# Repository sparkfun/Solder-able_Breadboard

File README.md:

Solder-able Breadboard
=======================

[ 
*Solder-able Breadboard(PRT-12070)*](https://www.sparkfun.com/products/12070)

This is a bare pcb that is the same size as a regular breadboard, along with the same connections and power rails.

Repository Contents
-------------------
* **/Hardware** - All Eagle design files (.brd, .sch)

License Information
-------------------
The hardware is released under [Creative Commons Share-alike 3.0](http://creativecommons.org/licenses/by-sa/3.0/).

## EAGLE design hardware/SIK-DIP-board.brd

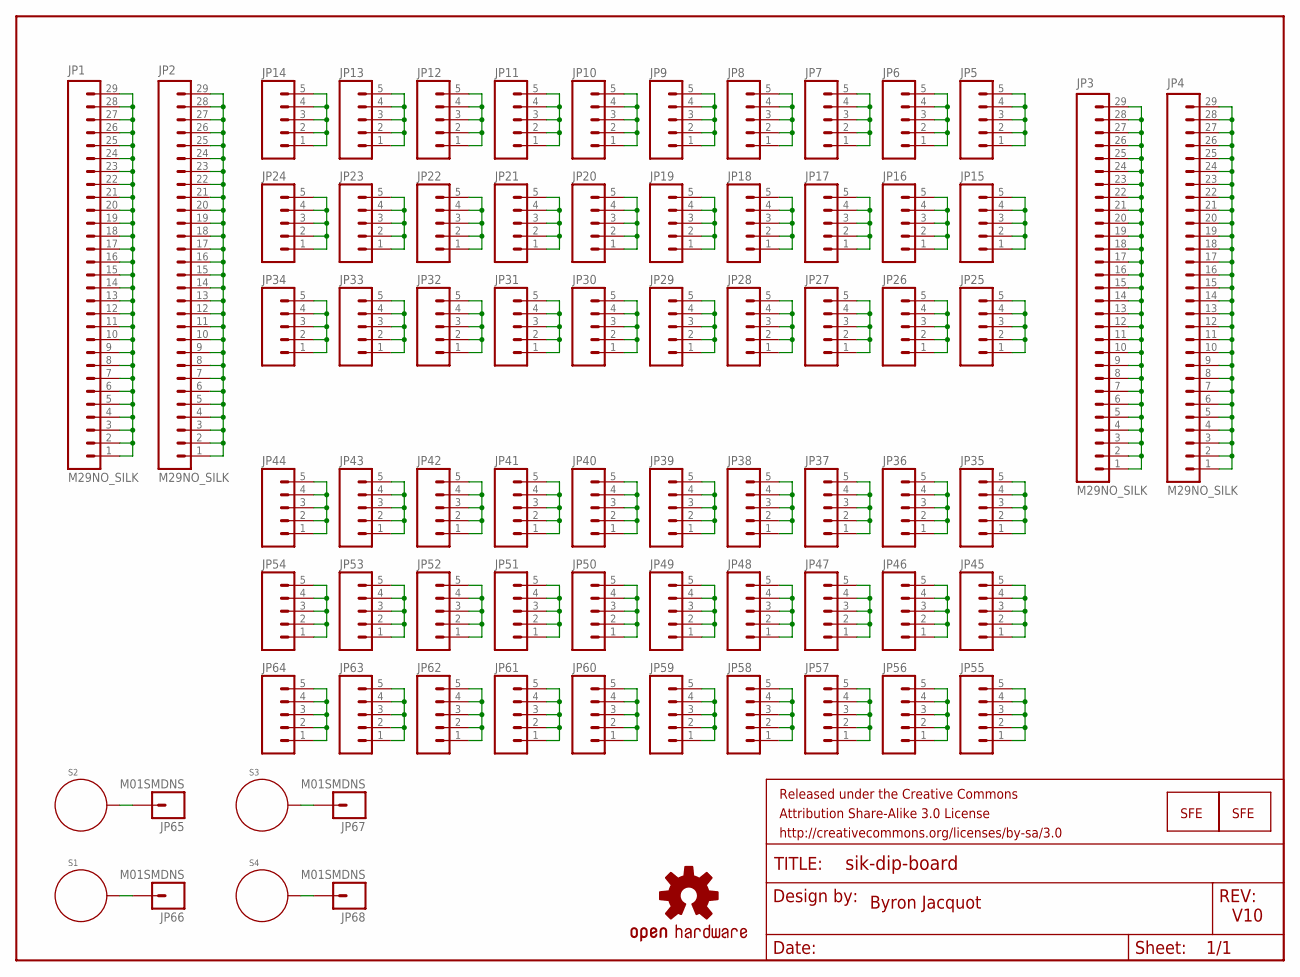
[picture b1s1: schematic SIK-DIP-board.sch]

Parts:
FRAME1: FRAME-LETTER; CREATIVE_COMMONS
JP1, JP2, JP3, JP4: M29NO_SILK; 1X29_NO_SILK
JP5, JP6, JP7, JP8, JP9, JP10, JP11, JP12, JP13, JP14, JP15, JP16, JP17, JP18, JP19, JP20, JP21, JP22, JP23, JP24, JP25, JP26, JP27, JP28, JP29, JP30, JP31, JP32, JP33, JP34, JP35, JP36, JP37, JP38, JP39, JP40, JP41, JP42, JP43, JP44, JP45, JP46, JP47, JP48, JP49, JP50, JP51, JP52, JP53, JP54, JP55, JP56, JP57, JP58, JP59, JP60, JP61, JP62, JP63, JP64: M05NO_SILK; 1X05_NO_SILK
JP65, JP66, JP67, JP68: M01SMDNS; 1X01NS
LOGO1: LOGO-SFECP; SFE-LOGO-FLAME-COPPER
LOGO2: LOGO-SFENEW; SFE-NEW-WEBLOGO
LOGO3: OSHW-LOGOS; OSHW-LOGO-S
S1, S2, S3, S4: STANDOFF_ELECTRICAL; STANDOFF-ELECTRICAL

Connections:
unnamed: JP1.1, JP1.2, JP1.3, JP1.4, JP1.5, JP1.6, JP1.7, JP1.8, JP1.9, JP1.10, JP1.11, JP1.12, JP1.13, JP1.14, JP1.15, JP1.16, JP1.17, JP1.18, JP1.19, JP1.20, JP1.21, JP1.22, JP1.23, JP1.24, JP1.25, JP1.26, JP1.27, JP1.28, JP1.29
unnamed: JP2.1, JP2.2, JP2.3, JP2.4, JP2.5, JP2.6, JP2.7, JP2.8, JP2.9, JP2.10, JP2.11, JP2.12, JP2.13, JP2.14, JP2.15, JP2.16, JP2.17, JP2.18, JP2.19, JP2.20, JP2.21, JP2.22, JP2.23, JP2.24, JP2.25, JP2.26, JP2.27, JP2.28, JP2.29
unnamed: JP3.1, JP3.2, JP3.3, JP3.4, JP3.5, JP3.6, JP3.7, JP3.8, JP3.9, JP3.10, JP3.11, JP3.12, JP3.13, JP3.14, JP3.15, JP3.16, JP3.17, JP3.18, JP3.19, JP3.20, JP3.21, JP3.22, JP3.23, JP3.24, JP3.25, JP3.26, JP3.27, JP3.28, JP3.29
unnamed: JP4.1, JP4.2, JP4.3, JP4.4, JP4.5, JP4.6, JP4.7, JP4.8, JP4.9, JP4.10, JP4.11, JP4.12, JP4.13, JP4.14, JP4.15, JP4.16, JP4.17, JP4.18, JP4.19, JP4.20, JP4.21, JP4.22, JP4.23, JP4.24, JP4.25, JP4.26, JP4.27, JP4.28, JP4.29
unnamed: JP10.1, JP10.2, JP10.3, JP10.4, JP10.5
unnamed: JP5.1, JP5.2, JP5.3, JP5.4, JP5.5
unnamed: JP6.1, JP6.2, JP6.3, JP6.4, JP6.5
unnamed: JP7.1, JP7.2, JP7.3, JP7.4, JP7.5
unnamed: JP8.1, JP8.2, JP8.3, JP8.4, JP8.5
unnamed: JP9.1, JP9.2, JP9.3, JP9.4, JP9.5
unnamed: JP11.1, JP11.2, JP11.3, JP11.4, JP11.5
unnamed: JP12.1, JP12.2, JP12.3, JP12.4, JP12.5
unnamed: JP13.1, JP13.2, JP13.3, JP13.4, JP13.5
unnamed: JP14.1, JP14.2, JP14.3, JP14.4, JP14.5
unnamed: JP15.1, JP15.2, JP15.3, JP15.4, JP15.5
unnamed: JP16.1, JP16.2, JP16.3, JP16.4, JP16.5
unnamed: JP17.1, JP17.2, JP17.3, JP17.4, JP17.5
unnamed: JP18.1, JP18.2, JP18.3, JP18.4, JP18.5
unnamed: JP19.1, JP19.2, JP19.3, JP19.4, JP19.5
unnamed: JP20.1, JP20.2, JP20.3, JP20.4, JP20.5
unnamed: JP21.1, JP21.2, JP21.3, JP21.4, JP21.5
unnamed: JP22.1, JP22.2, JP22.3, JP22.4, JP22.5
unnamed: JP23.1, JP23.2, JP23.3, JP23.4, JP23.5
unnamed: JP24.1, JP24.2, JP24.3, JP24.4, JP24.5
unnamed: JP25.1, JP25.2, JP25.3, JP25.4, JP25.5
unnamed: JP26.1, JP26.2, JP26.3, JP26.4, JP26.5
unnamed: JP27.1, JP27.2, JP27.3, JP27.4, JP27.5
unnamed: JP28.1, JP28.2, JP28.3, JP28.4, JP28.5
unnamed: JP29.1, JP29.2, JP29.3, JP29.4, JP29.5
unnamed: JP30.1, JP30.2, JP30.3, JP30.4, JP30.5
unnamed: JP31.1, JP31.2, JP31.3, JP31.4, JP31.5
unnamed: JP32.1, JP32.2, JP32.3, JP32.4, JP32.5
unnamed: JP33.1, JP33.2, JP33.3, JP33.4, JP33.5
unnamed: JP34.1, JP34.2, JP34.3, JP34.4, JP34.5
unnamed: JP35.1, JP35.2, JP35.3, JP35.4, JP35.5
unnamed: JP36.1, JP36.2, JP36.3, JP36.4, JP36.5
unnamed: JP37.1, JP37.2, JP37.3, JP37.4, JP37.5
unnamed: JP38.1, JP38.2, JP38.3, JP38.4, JP38.5
unnamed: JP39.1, JP39.2, JP39.3, JP39.4, JP39.5
unnamed: JP40.1, JP40.2, JP40.3, JP40.4, JP40.5
unnamed: JP41.1, JP41.2, JP41.3, JP41.4, JP41.5
unnamed: JP42.1, JP42.2, JP42.3, JP42.4, JP42.5
unnamed: JP43.1, JP43.2, JP43.3, JP43.4, JP43.5
unnamed: JP44.1, JP44.2, JP44.3, JP44.4, JP44.5
unnamed: JP45.1, JP45.2, JP45.3, JP45.4, JP45.5
unnamed: JP46.1, JP46.2, JP46.3, JP46.4, JP46.5
unnamed: JP47.1, JP47.2, JP47.3, JP47.4, JP47.5
unnamed: JP48.1, JP48.2, JP48.3, JP48.4, JP48.5
unnamed: JP49.1, JP49.2, JP49.3, JP49.4, JP49.5
unnamed: JP50.1, JP50.2, JP50.3, JP50.4, JP50.5
unnamed: JP51.1, JP51.2, JP51.3, JP51.4, JP51.5
unnamed: JP52.1, JP52.2, JP52.3, JP52.4, JP52.5
unnamed: JP53.1, JP53.2, JP53.3, JP53.4, JP53.5
unnamed: JP54.1, JP54.2, JP54.3, JP54.4, JP54.5
unnamed: JP55.1, JP55.2, JP55.3, JP55.4, JP55.5
unnamed: JP56.1, JP56.2, JP56.3, JP56.4, JP56.5
unnamed: JP57.1, JP57.2, JP57.3, JP57.4, JP57.5
unnamed: JP58.1, JP58.2, JP58.3, JP58.4, JP58.5
unnamed: JP59.1, JP59.2, JP59.3, JP59.4, JP59.5
unnamed: JP60.1, JP60.2, JP60.3, JP60.4, JP60.5
unnamed: JP61.1, JP61.2, JP61.3, JP61.4, JP61.5
unnamed: JP62.1, JP62.2, JP62.3, JP62.4, JP62.5
unnamed: JP63.1, JP63.2, JP63.3, JP63.4, JP63.5
unnamed: JP64.1, JP64.2, JP64.3, JP64.4, JP64.5
unnamed: JP65.1, S2.P1
unnamed: JP66.1, S1.P1
unnamed: JP67.1, S3.P1
unnamed: JP68.1, S4.P1

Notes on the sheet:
Byron Jacquot
V10

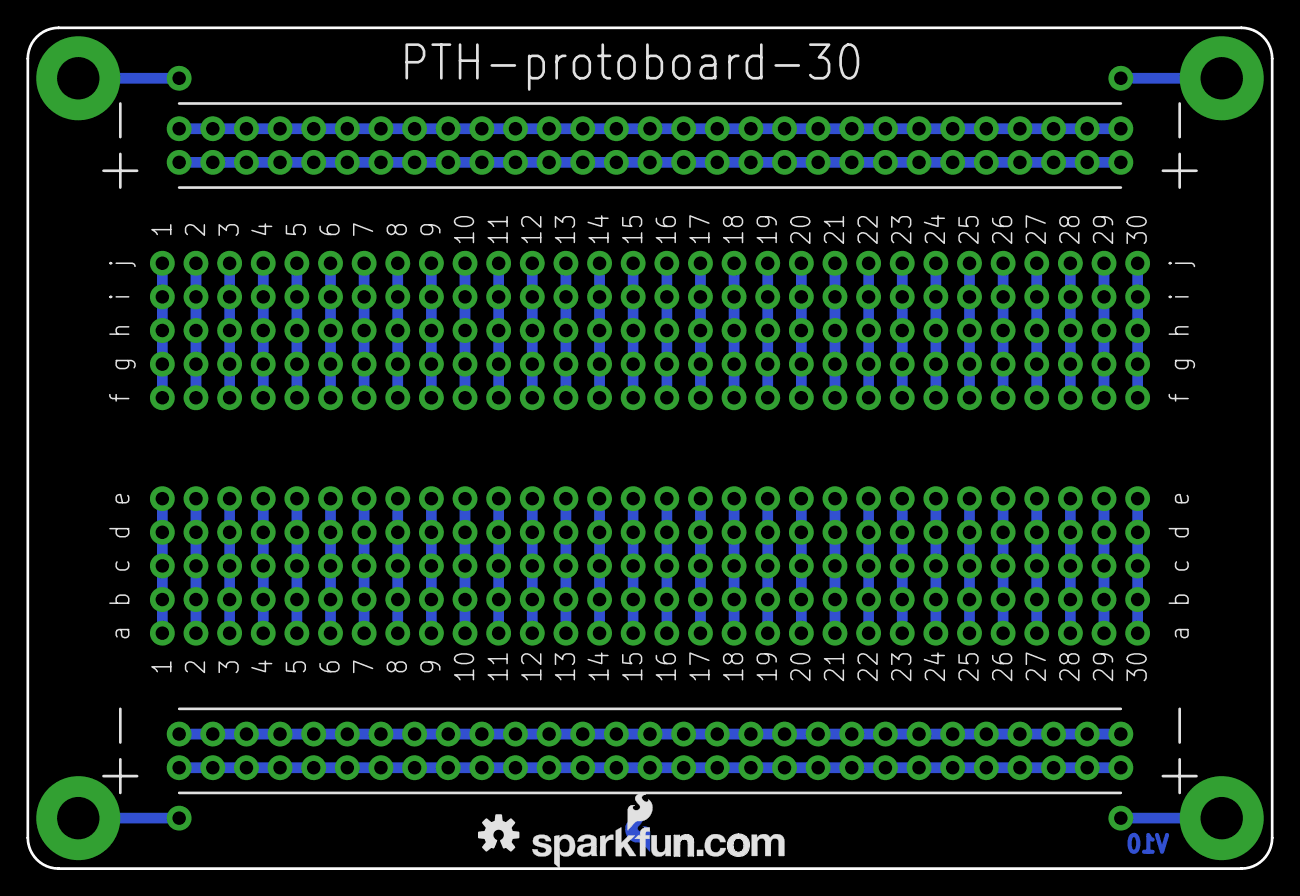
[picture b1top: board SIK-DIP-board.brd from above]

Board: 2 copper layers, 94.0 x 63.5 mm, 76 parts (1 on the bottom side), 68 nets.

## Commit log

2013-09-19 Initial commit.
2013-09-19 Added pads to allow grounding via mounting holes.
2013-09-20 Rounding corners.
2013-09-23 Amended following group review
    Adjusted size so silk doesn't overlap mounting holes.
    Duplicated top silk on bottom.
    Added name.
2013-09-24 Approving DRC error in FLAME-COPPER dimensions
2013-11-21 Changed after reviewing prototype
    Reversed text on bottom silk layer.
    Shrunk overall dimension.
2013-12-26 Adding README
2025-06-27 Update README.md
    Updating link

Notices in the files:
parts and their libraries:
SparkFun-Aesthetics: Licensing: CC v3.0 Share-Alike You are welcome to use this library for commercial purposes.
SparkFun-Aesthetics: Released under the Creative Commons Attribution Share-Alike 3.0 License
SparkFun-Aesthetics: Released under the Creative Commons
